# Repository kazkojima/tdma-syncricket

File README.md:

# TDMA with synchronized crickets

No documents yet

## Tree

* grc/: gnuRadio file
* wav/: Recorded .wav file
* chirpset/: Chirp .wav and the corresponding matched filter .cvd files
* dataset/: Range profile logmag files
* tdma/: TDMA julia programs
* tools/: Misc. tools

* hardware/: KiCad files for syncricket board
* firmware/: esp-idf projects for syncricket and synctrig firmwares

[> Links
-------------

[1] Michael Robinson, [web pages](https://www.drmichaelrobinson.net/research.html)
[Sound Card Sonar](https://www.drmichaelrobinson.net/demos.html#sonar)

[2] Michael Robinson, Topological Signal Processing, Springer 2014, [DOI](https://doi.org/10.1007/978-3-642-36104-3)

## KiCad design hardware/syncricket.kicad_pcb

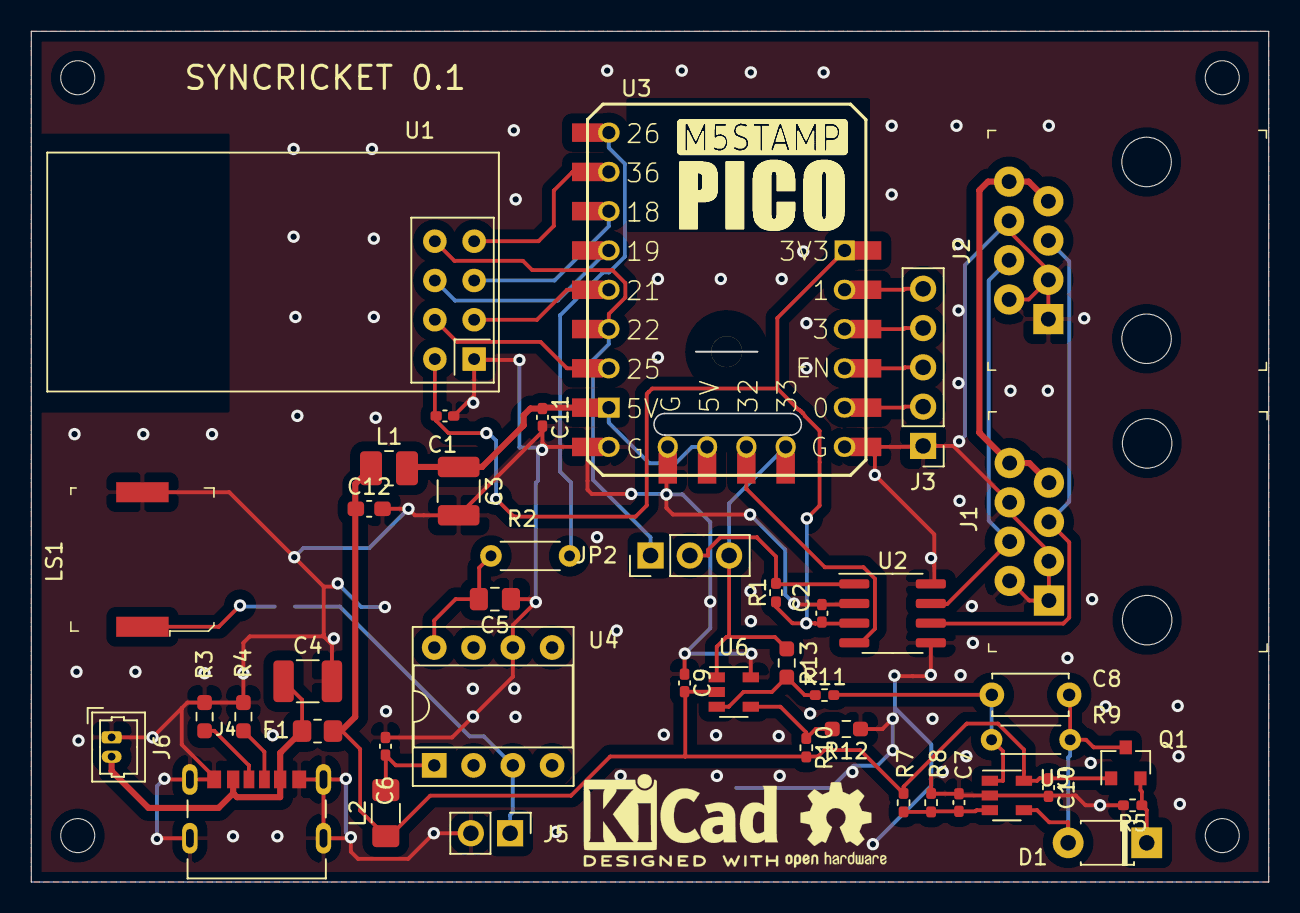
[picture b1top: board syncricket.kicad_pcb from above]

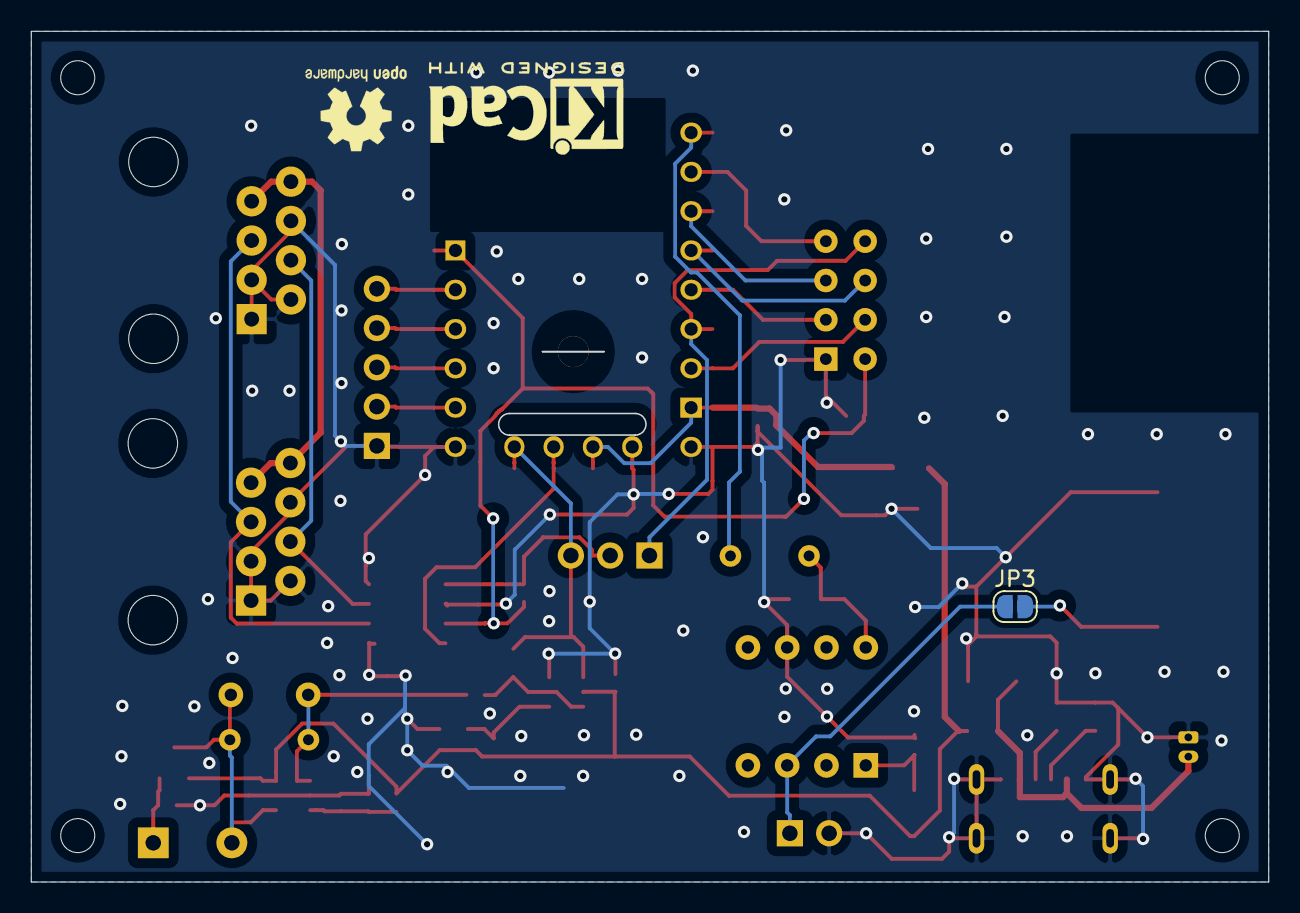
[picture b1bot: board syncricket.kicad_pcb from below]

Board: 2 copper layers, 80.0 x 55.0 mm, 48 parts (3 on the bottom side), 34 nets.

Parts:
C1, C2, C9, C10, C11: 0.1u; C_0402_1005Metric_Pad0.74x0.62mm_HandSolder
C3: 220u; C_1210_3225Metric_Pad1.33x2.70mm_HandSolder
C4: 100u; C_1210_3225Metric_Pad1.33x2.70mm_HandSolder
C5: 103; C_0805_2012Metric_Pad1.18x1.45mm_HandSolder
C6: 2.2u; C_0402_1005Metric_Pad0.74x0.62mm_HandSolder
C7: 1u; C_0402_1005Metric_Pad0.74x0.62mm_HandSolder
C8: 1pF; C_Disc_D4.7mm_W2.5mm_P5.00mm
C12: 22u; C_0603_1608Metric_Pad1.08x0.95mm_HandSolder
D1: S6775-01; D_T-1_P5.08mm_Horizontal
F1: Polyfuse_Small; R_0805_2012Metric_Pad1.20x1.40mm_HandSolder
J1, J2: 54602-908LF; Ethernet_Jack_54602-908LF
J3: Conn_01x05; PinHeader_1x05_P2.54mm_Vertical
J4: UJC-HP-3-SMT-TR; CUI_UJC-HP-3-SMT-TR
J5: Conn_01x02; PinHeader_1x02_P2.54mm_Vertical
J6: Conn_01x02; Molex_PicoBlade_53047-0210_1x02_P1.25mm_Vertical
JP2: Jumper_3_Bridged12_modified; PinHeader_1x03_P2.54mm_Vertical
JP3: SolderJumper_2_Open; SolderJumper-2_P1.3mm_Open_RoundedPad1.0x1.5mm
L1: 1.5uH; L_1008_2520Metric_Pad1.43x2.20mm_HandSolder
L2: 27uH; L_1206_3216Metric_Pad1.42x1.75mm_HandSolder
LS1: Speaker_Ultrasound; Piezo_9x9mm_PKMCS0909E4000-R1
Q1: CPH3910; SOT-23
R1, R5, R11: 4.99k; R_0402_1005Metric_Pad0.72x0.64mm_HandSolder
R2: 330; R_Axial_DIN0204_L3.6mm_D1.6mm_P5.08mm_Horizontal
R3, R4: 5.1k; R_0603_1608Metric_Pad0.98x0.95mm_HandSolder
R7, R8: 5k; R_0402_1005Metric_Pad0.72x0.64mm_HandSolder
R9: 1M; R_Axial_DIN0204_L3.6mm_D1.6mm_P5.08mm_Horizontal
R10: 10k; R_0402_1005Metric_Pad0.72x0.64mm_HandSolder
R12: 1k; R_0603_1608Metric_Pad0.98x0.95mm_HandSolder
R13: 47k; R_0603_1608Metric_Pad0.98x0.95mm_HandSolder
REF001, REF003: KiCad-Logo2_5mm_SilkScreen
REF002, REF004: OSHW-Logo2_7.3x6mm_SilkScreen
U1: NRF24L01_Breakout; nRF24L01_Breakout
U2: MAX3051; SOIC-8_3.9x4.9mm_P1.27mm
U3: Stamp_Pico; StampPico_template
U4: LT1010; DIP-8_W7.62mm_Socket
U5: NJU77701; SOT-23-5
U6: MCP6566R; SOT-23-5

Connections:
+3V3: C1.1, C2.2, R1.1, U1.2, U2.3, U3.19
+5V: C9.2, C10.1, C12.1, F1.1, L1.1, L2.1, Q1.1, R7.2, R10.2, U5.5, U6.2
AUXSYN: JP2.3, R13.1, U3.13, U6.1
GND: C1.2, C2.1, C3.2, C4.2, C5.1, C6.1, C7.1, C9.1, C10.2, C11.2, C12.2, J1.1, J1.2, J1.3, J1.6, J2.1, J2.2, J2.3, J2.6, J3.1, J4.A12, J4.B12, J4.S1, J4.S2, J4.S3, J4.S4, J5.2, J6.1, LS1.2, R3.1, R4.1, R5.2, R8.1, R12.1, U1.1, U2.2, U2.5, U2.8, U3.9, U3.10, U3.14, U4.6, U5.2, U6.5
unnamed: C4.1, F1.2, J4.A9, J4.B9, J6.2
unnamed: C5.2, R2.2, U4.8
unnamed: C6.2, L2.2, U4.1
unnamed: C7.2, R7.1, R8.2, U5.3
unnamed: C8.1, R9.1, R11.2, U5.1
unnamed: C8.2, D1.2, Q1.3, R9.2, U5.4
unnamed: C3.1, C11.1, L1.2, U3.8, U3.11
unnamed: D1.1, Q1.2, R5.1
unnamed: J1.4, J2.4, U2.7
unnamed: J1.5, J2.5, U2.6
unnamed: J1.7, J1.8, J2.7, J2.8
unnamed: J3.2, U3.15
unnamed: J3.3, U3.16
unnamed: J3.4, U3.17
unnamed: J3.5, U3.18
unnamed: J4.A5, R3.2
unnamed: J4.B5, R4.2
unnamed: J5.1, JP3.1, U4.3
unnamed: JP2.1, U1.8, U3.6
unnamed: JP2.2, R1.2, U2.1
unnamed: JP3.2, LS1.1
unnamed: R2.1, U3.1
unnamed: R10.1, R12.2, U6.4
unnamed: R11.1, R13.2, U6.3
unnamed: U1.3, U3.5
unnamed: U1.4, U3.7
unnamed: U1.5, U3.3
unnamed: U1.6, U3.4
unnamed: U1.7, U3.2
unnamed: U2.4, U3.12

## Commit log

2022-08-22 Initial commit.
2022-08-22 Add LICENSE.
2022-08-22 Fix README.md.
2022-08-23 Add firmwares.
